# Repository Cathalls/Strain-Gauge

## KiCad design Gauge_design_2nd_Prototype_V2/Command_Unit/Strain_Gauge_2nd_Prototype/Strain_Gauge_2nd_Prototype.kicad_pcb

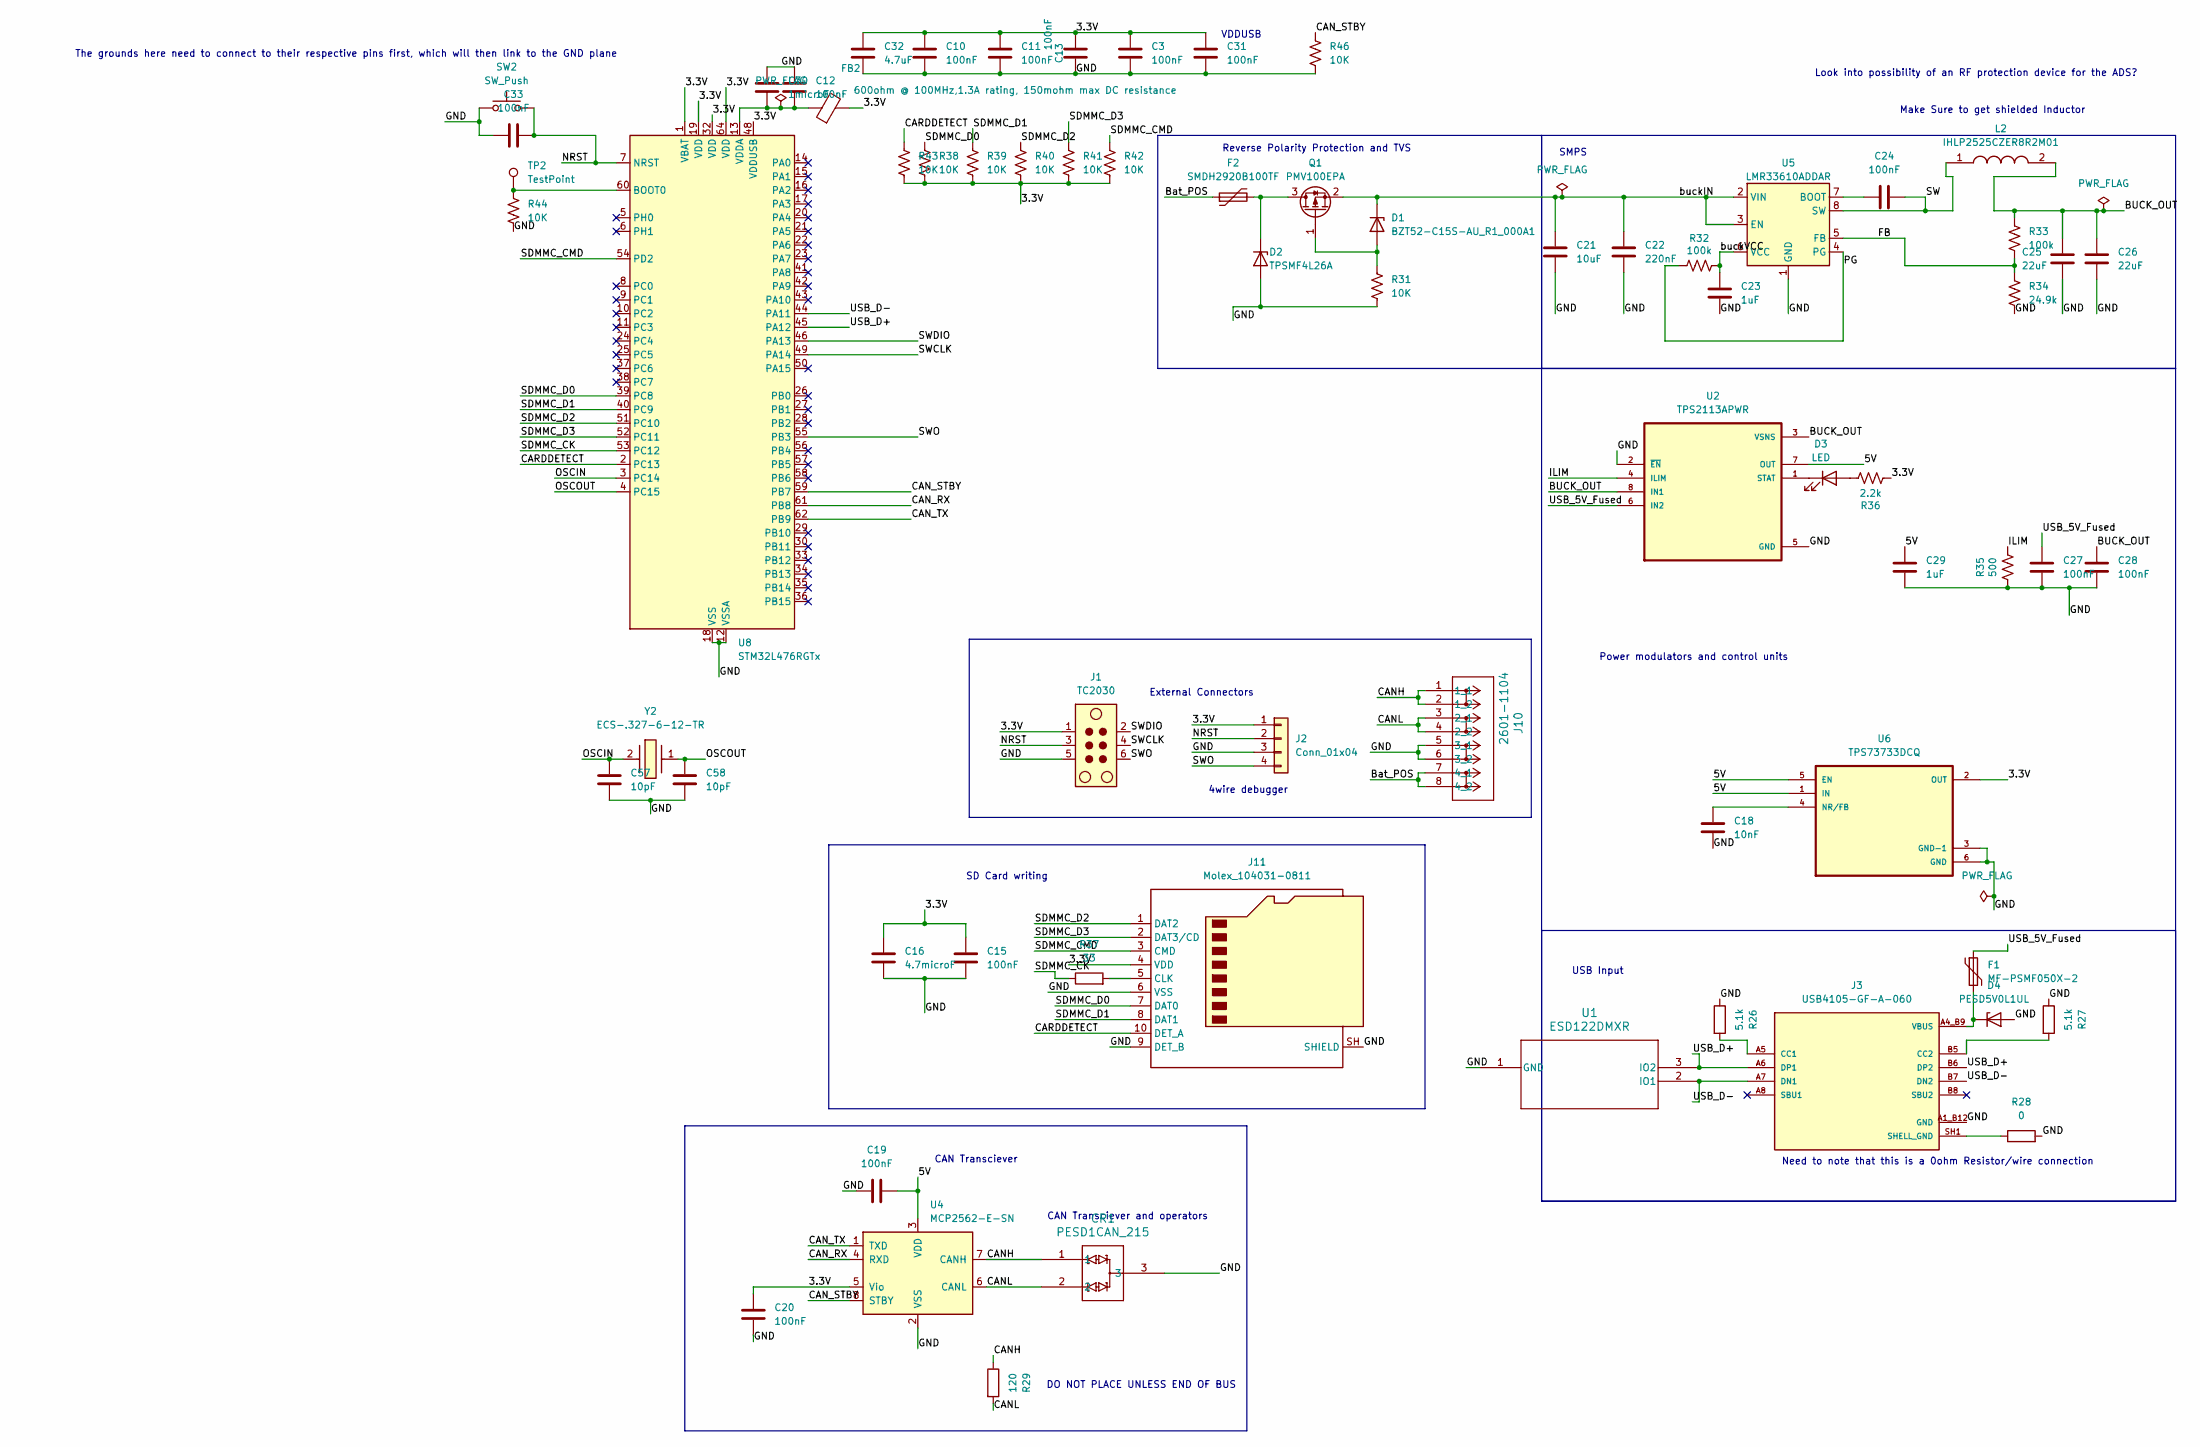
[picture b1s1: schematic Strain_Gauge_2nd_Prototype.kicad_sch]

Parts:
C3, C10, C11, C12, C13, C15, C19, C20, C24, C27, C28, C31, C33: 100nF; C_0402_1005Metric_Pad0.74x0.62mm_HandSolder
C16: 4.7microF; C_0603_1608Metric_Pad1.08x0.95mm_HandSolder
C18: 10nF; C_0402_1005Metric_Pad0.74x0.62mm_HandSolder
C21: 10uF; C_0805_2012Metric_Pad1.18x1.45mm_HandSolder
C22: 220nF; C_0402_1005Metric_Pad0.74x0.62mm_HandSolder
C23, C29: 1uF; C_1206_3216Metric_Pad1.33x1.80mm_HandSolder
C25, C26: 22uF; C_1206_3216Metric_Pad1.33x1.80mm_HandSolder
C30: 1microF; C_1206_3216Metric_Pad1.33x1.80mm_HandSolder
C32: 4.7uF; C_0603_1608Metric_Pad1.08x0.95mm_HandSolder
C57, C58: 10pF; C_0603_1608Metric_Pad1.08x0.95mm_HandSolder
CR1: PESD1CAN_215; SOT23_PESD1_NEX
D1: BZT52-C15S-AU_R1_000A1; D_SOD-323_HandSoldering
D2: TPSMF4L26A; D_SOD-123F
D3: LED; LED_0402_1005Metric
D4: PESD5V0L1UL; D_SOD-882
F1: MF-PSMF050X-2; Fuse_0805_2012Metric_Pad1.15x1.40mm_HandSolder
F2: SMDH2920B100TF; D_SOD-882
FB2: 600ohm @ 100MHz,1.3A rating, 150mohm max DC resis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; L_0603_1608Metric_Pad1.05x0.95mm_HandSolder
J1: TC2030; Tag-Connect_TC2030-IDC-NL_2x03_P1.27mm_Vertical
J2: Conn_01x04; SolderWire-0.25sqmm_1x04_P4.5mm_D0.65mm_OD2mm
J3: USB4105-GF-A-060; GCT_USB4105-GF-A-060; PARTREV B3
J10: 2601-1104; CONN4_2601-1104_WAG
J11: Molex_104031-0811; microSD_HC_Molex_104031-0811
L2: IHLP2525CZER8R2M01; INDPM6965X300N; Mouser Part Number 70-IHLP2525CZER8R2M1
Q1: PMV100EPA; SOT-23_Handsoldering
R26, R27: 5.1k; R_0402_1005Metric_Pad0.72x0.64mm_HandSolder
R28: 0; R_0402_1005Metric_Pad0.72x0.64mm_HandSolder
R29: 120; R_0402_1005Metric
R31, R38, R39, R40, R41, R42, R43, R44, R46: 10K; R_0402_1005Metric_Pad0.72x0.64mm_HandSolder
R32: 100k; R_0402_1005Metric_Pad0.72x0.64mm_HandSolder
R33: 100k; R_0402_1005Metric
R34: 24.9k; R_0402_1005Metric_Pad0.72x0.64mm_HandSolder
R35: 500; R_0402_1005Metric_Pad0.72x0.64mm_HandSolder
R36: 2.2k; R_0402_1005Metric_Pad0.72x0.64mm_HandSolder
R37: 33; R_0402_1005Metric_Pad0.72x0.64mm_HandSolder
SW2: SW_Push; SW_PUSH_6mm
TP2: TestPoint; TestPoint_Pad_D1.5mm
U1: ESD122DMXR; DMX3_TEX
U2: TPS2113APWR; SOP65P640X120-8N
U4: MCP2562-E-SN; SOIC-8_3.9x4.9mm_P1.27mm
U5: LMR33610ADDAR; Texas_HSOP-8-1EP_3.9x4.9mm_P1.27mm_ThermalVias
U6: TPS73733DCQ; SOT127P706X180-6N
U8: STM32L476RGTx; LQFP-64_10x10mm_P0.5mm
Y2: ECS-.327-6-12-TR; ECS327612TR; Mouser Part Number 520-ECS-.327-6-12-TR

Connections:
/3.3V: C3.1, C10.2, C11.2, C13.2, C15.1, C16.1, C20.1, C31.1, C32.1, FB2.2, J1.1, J2.1, J11.4 (VDD), R36.1, R38.2, R39.2, R40.2, R41.2, R42.2, R43.2, U4.5 (Vio), U6.2 (OUT), U8.1 (VBAT), U8.19 (VDD), U8.32 (VDD), U8.48 (VDDUSB), U8.64 (VDD)
/5V: C19.2, C29.1, U2.7 (OUT), U4.3 (VDD), U6.1 (IN), U6.5 (EN)
/BUCK_OUT: C25.1, C26.1, C28.1, L2.2, R33.1, U2.3 (VSNS), U2.8 (IN1)
/Bat_POS: F2.1, J10.7 (4_1), J10.8 (4_2)
/CANH: CR1.1, J10.1 (1_1), J10.2 (1_2), R29.1, U4.7 (CANH)
/CANL: CR1.2, J10.3 (2_1), J10.4 (2_2), R29.2, U4.6 (CANL)
/CAN_RX: U4.4 (RXD), U8.61 (PB8)
/CAN_STBY: R46.1, U4.8 (STBY), U8.59 (PB7)
/CAN_TX: U4.1 (TXD), U8.62 (PB9)
/CARDDETECT: J11.10 (DET_A), R43.1, U8.2 (PC13)
/FB: R33.2, R34.1, U5.5 (FB)
/ILIM: R35.2, U2.4 (ILIM)
/NRST: C33.1, J1.3, J2.2, SW2.2, U8.7 (NRST)
/OSCIN: C57.1, U8.3 (PC14), Y2.2 (OUT/IN_2)
/OSCOUT: C58.1, U8.4 (PC15), Y2.1
/PG: R32.1, U5.4 (PG)
/SDMMC_CK: R37.1, U8.53 (PC12)
/SDMMC_CMD: J11.3 (CMD), R42.1, U8.54 (PD2)
/SDMMC_D0: J11.7 (DAT0), R38.1, U8.39 (PC8)
/SDMMC_D1: J11.8 (DAT1), R39.1, U8.40 (PC9)
/SDMMC_D2: J11.1 (DAT2), R40.1, U8.51 (PC10)
/SDMMC_D3: J11.2 (DAT3/CD), R41.1, U8.52 (PC11)
/SW: C24.2, L2.1, U5.8 (SW)
/SWCLK: J1.4, U8.49 (PA14)
/SWDIO: J1.2, U8.46 (PA13)
/SWO: J1.6, J2.4, U8.55 (PB3)
/USB_5V_Fused: C27.1, F1.1, U2.6 (IN2)
/USB_D+: J3.A6 (DP1), J3.B6 (DP2), U1.3 (IO2), U8.45 (PA12)
/USB_D-: J3.A7 (DN1), J3.B7 (DN2), U1.2 (IO1), U8.44 (PA11)
/buckIN: C21.1, C22.1, D1.1 (K), Q1.2 (S), U5.2 (VIN), U5.3 (EN)
/buckVCC: C23.1, R32.2, U5.6 (VCC)
GND: C3.2, C10.1, C11.1, C12.2, C13.1, C15.2, C16.2, C18.2, C19.1, C20.2, C21.2, C22.2, C23.2, C25.2, C26.2, C27.2, C28.2, C29.2, C30.1, C31.2, C32.2, C33.2, C57.2, C58.2, CR1.3, D2.2 (A), D4.2 (A), J1.5, J2.3, J3.A1_B12 (GND), J3.B1_A12 (GND), J10.5 (3_1), J10.6 (3_2), J11.6 (VSS), J11.9 (DET_B), J11.SH (SHIELD), R26.1, R27.1, R28.2, R31.2, R34.2, R35.1, R44.2, R46.2, SW2.1, U1.1 (GND), U2.2 (~EN), U2.5 (GND), U4.2 (VSS), U5.1 (GND), U5.9 (GND), U6.3 (GND-1), U6.6 (GND), U8.12 (VSSA), U8.18 (VSS), U8.31 (VSS), U8.47 (VSS), U8.63 (VSS)
unnamed: D1.2 (A), Q1.1 (G), R31.1
unnamed: D2.1 (K), F2.2, Q1.3 (D)
unnamed: D3.2 (A), R36.2
unnamed: D3.1 (K), U2.1 (STAT)
unnamed: J3.A5 (CC1), R26.2
unnamed: J3.B5 (CC2), R27.2
unnamed: J11.5 (CLK), R37.2
unnamed: C24.1, U5.7 (BOOT)
unnamed: C18.1, U6.4 (NR/FB)
unnamed: R44.1, TP2.1 (1_1), U8.60 (BOOT0)
unnamed: C12.1, C30.2, FB2.1, U8.13 (VDDA)
SHELL_GND: J3.SH1 (SHELL_GND), J3.SH2 (SHELL_GND), J3.SH3 (SHELL_GND), J3.SH4 (SHELL_GND), R28.1
VBUS: D4.1 (K), F1.2, J3.A4_B9 (VBUS), J3.B4_A9 (VBUS)

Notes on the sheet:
SMPS
Need to note that this is a 0ohm Resistor/wire connection
VDDUSB
Power modulators and control units
Make Sure to get shielded Inductor
Reverse Polarity Protection and TVS
4wire debugger
USB Input
DO NOT PLACE UNLESS END OF BUS
Look into possibility of an RF protection device for the ADS?
SD Card writing
CAN Transciever and operators
External Connectors
CAN Transciever
The grounds here need to connect to their respective pins first, which will then link to the GND plane

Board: 2 copper layers, 68 parts (0 on the bottom side), 45 nets, no tracks yet.

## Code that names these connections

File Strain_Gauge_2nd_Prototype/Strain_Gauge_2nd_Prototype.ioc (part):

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Mcu.Name=STM32L476R(C-E-G)Tx
Mcu.Package=LQFP64
Mcu.UserName=STM32L476RGTx
PA11.Mode=Device_Only
PA11.Signal=USB_OTG_FS_DM
PA12.Mode=Device_Only
PA12.Signal=USB_OTG_FS_DP
PA13\ (JTMS-SWDIO).Mode=Serial_Wire
PA13\ (JTMS-SWDIO).Signal=SYS_JTMS-SWDIO
PA14\ (JTCK-SWCLK).Mode=Serial_Wire
PA14\ (JTCK-SWCLK).Signal=SYS_JTCK-SWCLK
PA4.GPIOParameters=GPIO_Label
PA4.GPIO_Label=ADC_CS
PA4.Signal=GPIO_Output
PA5.Mode=Full_Duplex_Master
PA5.Signal=SPI1_SCK
PA6.Mode=Full_Duplex_Master
PA6.Signal=SPI1_MISO
PA7.Mode=Full_Duplex_Master
PA7.Signal=SPI1_MOSI
PB0.GPIOParameters=GPIO_Label,GPIO_ModeDefaultEXTI
PB0.GPIO_Label=ADC_DRDY
PB0.GPIO_ModeDefaultEXTI=GPIO_MODE_IT_FALLING
PB0.Signal=GPXTI0
PB1.GPIOParameters=GPIO_Label
PB1.GPIO_Label=ADC_START
PB1.Signal=GPIO_Output
PB3\ (JTDO-TRACESWO).Signal=SYS_JTDO-SWO
PB7.GPIOParameters=GPIO_Label
PB7.GPIO_Label=CAN_STBY
PB7.Signal=GPXTI7
PB8.Mode=CAN_Activate
PB8.Signal=CAN1_RX
PB9.Mode=CAN_Activate
PB9.Signal=CAN1_TX
PC10.Mode=SD_4_bits_Wide_bus
PC10.Signal=SDMMC1_D2
PC11.Mode=SD_4_bits_Wide_bus
PC11.Signal=SDMMC1_D3
PC12.Mode=SD_4_bits_Wide_bus
PC12.Signal=SDMMC1_CK
PC13.GPIOParameters=GPIO_Label
PC13.GPIO_Label=CARDDETECT
PC13.Signal=GPXTI13
PC14-OSC32_IN\ (PC14).Mode=LSE-External-Oscillator
PC14-OSC32_IN\ (PC14).Signal=RCC_OSC32_IN
PC15-OSC32_OUT\ (PC15).Mode=LSE-External-Oscillator
PC15-OSC32_OUT\ (PC15).Signal=RCC_OSC32_OUT
PC4.GPIOParameters=GPIO_Label
PC4.GPIO_Label=ADCPWDN
PC4.Signal=GPXTI4
PC5.GPIOParameters=GPIO_Label
PC5.GPIO_Label=ADCRESET
PC5.Signal=GPXTI5
PC8.Mode=SD_4_bits_Wide_bus
PC8.Signal=SDMMC1_D0
PC9.Mode=SD_4_bits_Wide_bus
PC9.Signal=SDMMC1_D1
PD2.Mode=SD_4_bits_Wide_bus
PD2.Signal=SDMMC1_CMD
RCC.HSE_VALUE=8192000
RCC.SYSCLKFreq_VALUE=80000000
RCC.SYSCLKSource=RCC_SYSCLKSOURCE_PLLCLK
board=custom
